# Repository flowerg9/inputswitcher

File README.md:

## Audio Input Switcher

uses ATmega328P

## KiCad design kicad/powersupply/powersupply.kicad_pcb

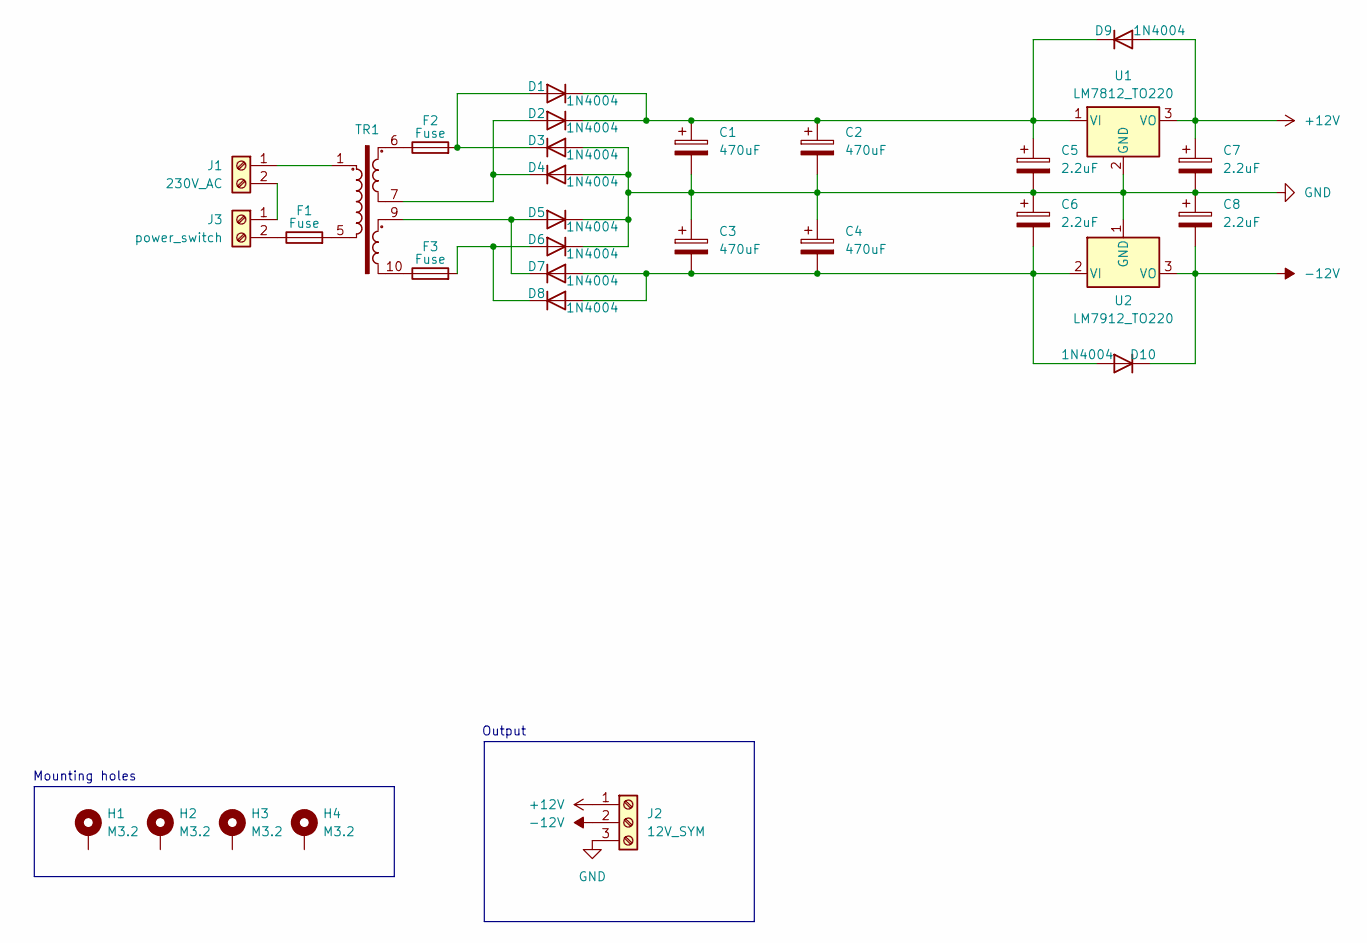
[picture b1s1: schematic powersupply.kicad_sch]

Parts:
C1, C2, C3, C4: 470uF; CP_Radial_D10.0mm_P5.00mm
C5, C6, C7, C8: 2.2uF; CP_EIA-3216-18_Kemet-A_HandSolder
D1, D2, D3, D4, D5, D6, D7, D8: 1N4004; D_DO-41_SOD81_P3.81mm_Vertical_AnodeUp
D9, D10: 1N4004; D_DO-41_SOD81_P12.70mm_Horizontal
F1, F2, F3: Fuse; Fuseholder_Clip-5x20mm_Littelfuse_111_Inline_P20.00x5.00mm_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
H1, H2, H3, H4: M3.2; MountingHole_3.2mm_M3_DIN965_Pad_TopBottom
J1: 230V_AC; TerminalBlock_MaiXu_MX126-5.0-02P_1x02_P5.00mm
J2: 12V_SYM; TerminalBlock_MaiXu_MX126-5.0-03P_1x03_P5.00mm
J3: power_switch; TerminalBlock_MaiXu_MX126-5.0-02P_1x02_P5.00mm
TR1: TEZ2.6-D-2; Transformer_Breve_TEZ-28x33
U1: LM7812_TO220; TO-220-3_Vertical
U2: LM7912_TO220; TO-220-3_Vertical

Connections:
+12V: C7.1, D9.2 (A), J2.1, U1.3 (VO)
-12V: C8.2, D10.1 (K), J2.2, U2.3 (VO)
GND: C1.2, C2.2, C3.1, C4.1, C5.2, C6.1, C7.2, C8.1, D3.2 (A), D4.2 (A), D5.1 (K), D6.1 (K), J2.3, U1.2 (GND), U2.1 (GND)
unnamed: D1.2 (A), D3.1 (K), F2.2
unnamed: C1.1, C2.1, C5.1, D1.1 (K), D2.1 (K), D9.1 (K), U1.1 (VI)
unnamed: D2.2 (A), D4.1 (K), TR1.7
unnamed: D5.2 (A), D7.1 (K), TR1.9
unnamed: D6.2 (A), D8.1 (K), F3.2
unnamed: C3.2, C4.2, C6.2, D7.2 (A), D8.2 (A), D10.2 (A), U2.2 (VI)
unnamed: F1.2, TR1.5
unnamed: F2.1, TR1.6
unnamed: F3.1, TR1.10
unnamed: J1.1, TR1.1
unnamed: J1.2, J3.1
unnamed: F1.1, J3.2

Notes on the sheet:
Mounting holes
Output

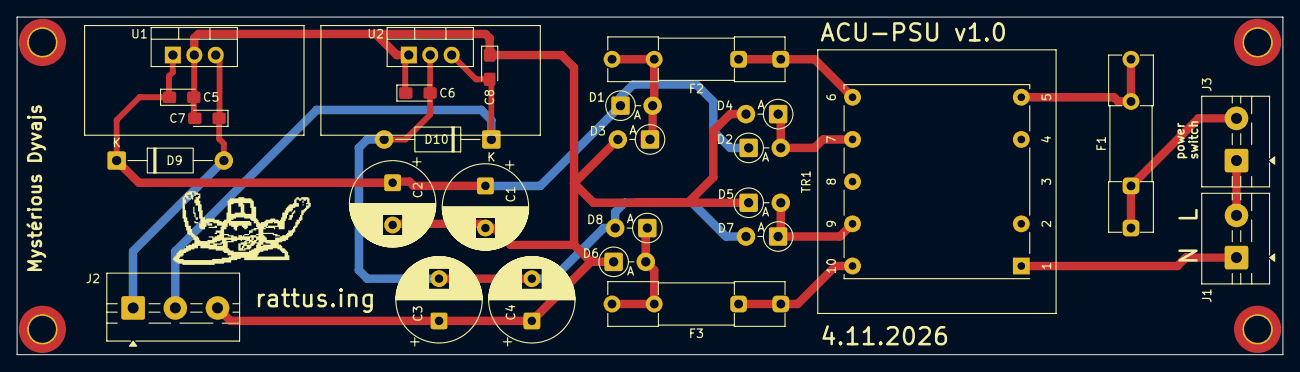
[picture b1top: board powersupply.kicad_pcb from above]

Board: 2 copper layers, 150.0 x 40.0 mm, 31 parts (0 on the bottom side), 15 nets.
